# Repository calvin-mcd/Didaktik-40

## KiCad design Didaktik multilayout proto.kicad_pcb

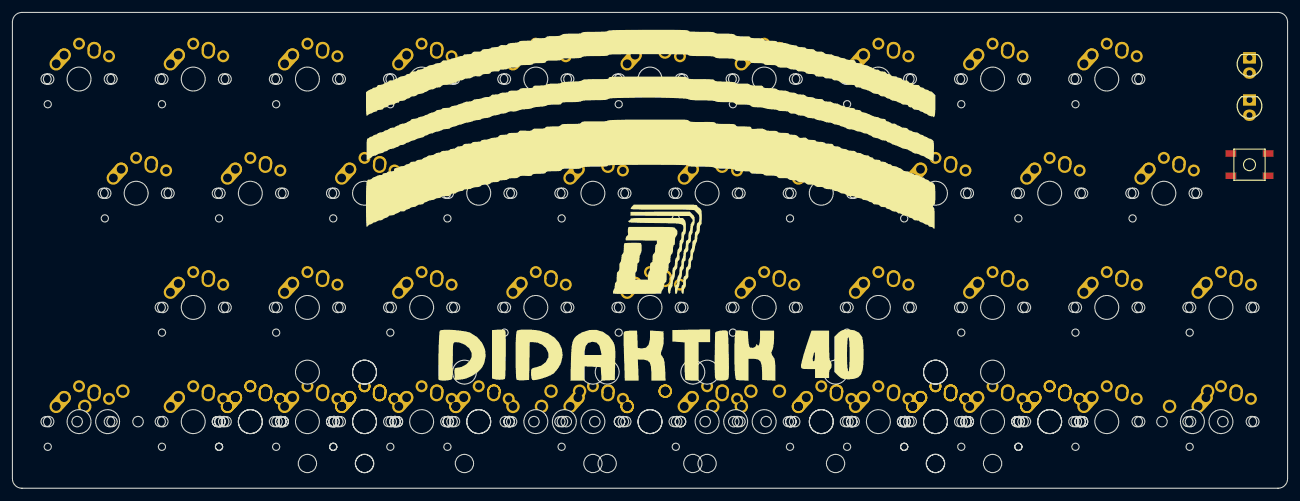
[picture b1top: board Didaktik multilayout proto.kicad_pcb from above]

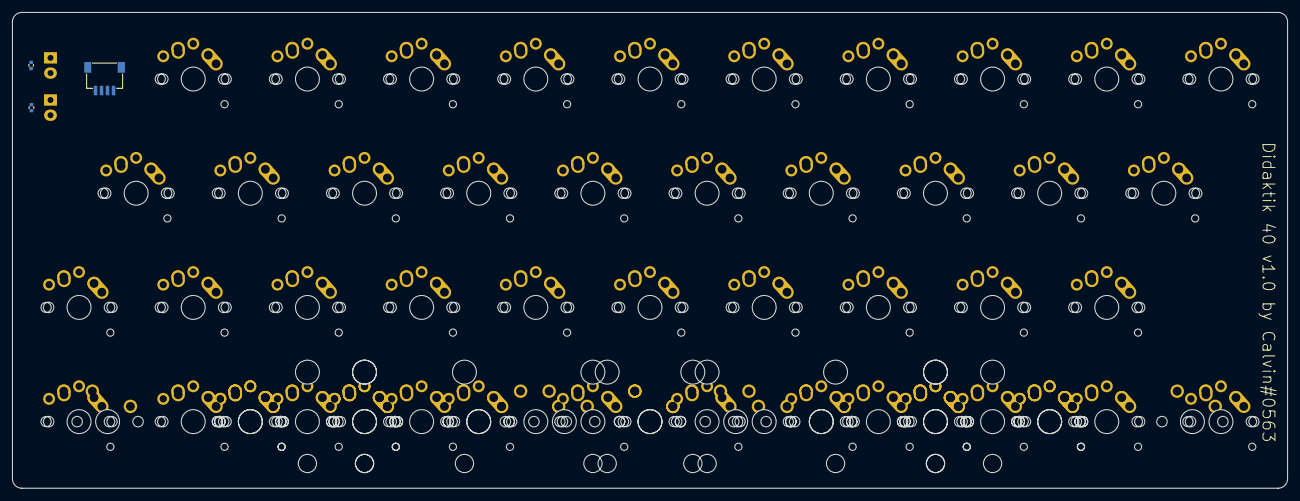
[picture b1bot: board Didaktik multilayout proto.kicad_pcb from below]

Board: 2 copper layers, 212.7 x 79.4 mm, 56 parts (3 on the bottom side), 12 nets, no tracks yet.

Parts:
D42, D43: LED; LED_3mm
J1: Conn_01x04_MountingPin; JST-SR-4
R8, R9: 220 ohm; R_0402_1005Metric
SW1: SW_Push; SKQG-1155865
SW2, SW3, SW4, SW6, SW7, SW8, SW9, SW9#2, SW9#3, SW9#4, SW9#5, SW10, SW11, SW12, SW13, SW13#2, SW13#3, SW13#4, SW13#5, SW14, SW15, SW16, SW17, SW17#2, SW17#3, SW18, SW19, SW20, SW21, SW21#2, SW21#3, SW22, SW23, SW24, SW25, SW26, SW27, SW28, SW29, SW30, SW31, SW32, SW33, SW34, SW35, SW36, SW37, SW38, SW39, SW40: SW_Push_45deg; MX-Alps-Choc-1U-NoLED

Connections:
COL0: SW2.1, SW3.1, SW4.1, SW6.1, SW7.1, SW8.1, SW9.1, SW9#2.1, SW9#3.1, SW9#4.1, SW9#5.1
COL1: SW10.1, SW11.1, SW12.1, SW13.1, SW13#2.1, SW13#3.1, SW13#4.1, SW13#5.1, SW14.1, SW15.1, SW16.1, SW17.1, SW17#2.1, SW17#3.1
COL2: SW18.1, SW19.1, SW20.1, SW21.1, SW21#2.1, SW21#3.1, SW22.1, SW23.1, SW24.1, SW25.1
COL3: SW26.1, SW27.1, SW28.1, SW29.1, SW30.1, SW31.1, SW32.1, SW33.1
COL4: SW34.1, SW35.1, SW36.1, SW37.1, SW38.1, SW39.1, SW40.1
GND: D42.1 (K), D43.1 (K), J1.4, SW1.1
unnamed: SW9.2, SW9#2.2, SW9#3.2, SW9#4.2, SW9#5.2
unnamed: SW13.2, SW13#2.2, SW13#3.2, SW13#4.2, SW13#5.2
unnamed: SW17.2, SW17#2.2, SW17#3.2
unnamed: SW21.2, SW21#2.2, SW21#3.2
unnamed: D42.2 (A), R8.2
unnamed: D43.2 (A), R9.2
